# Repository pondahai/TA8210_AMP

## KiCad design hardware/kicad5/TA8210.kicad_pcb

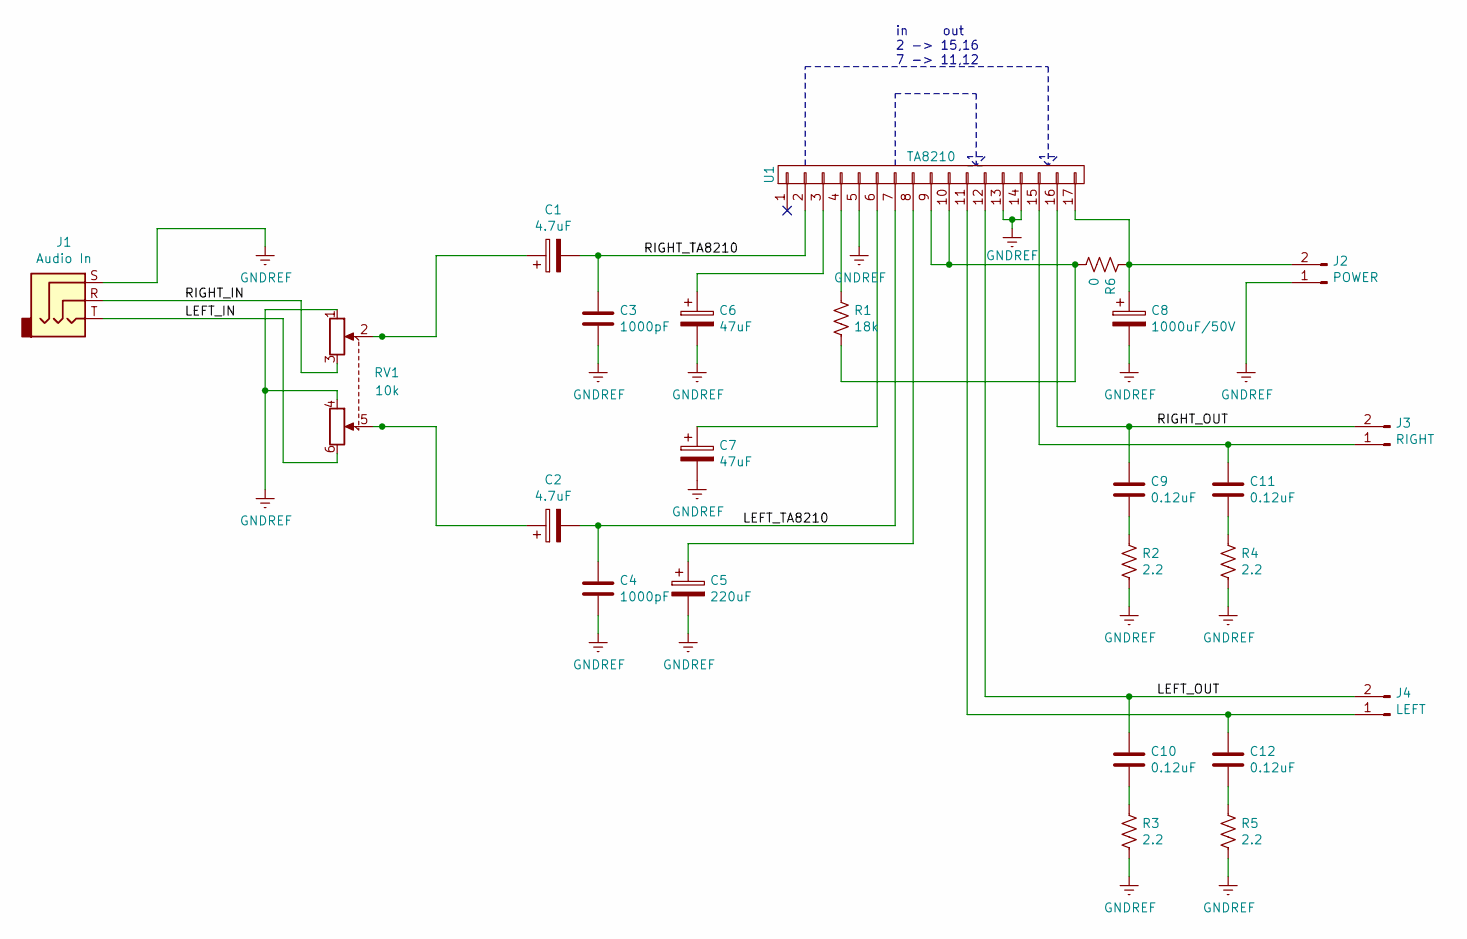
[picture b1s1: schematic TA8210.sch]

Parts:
C1, C2: 4.7uF; C_Rect_L13.0mm_W4.0mm_P10.00mm_FKS3_FKP3_MKS4
C3, C4: 1000pF; C_Disc_D10.5mm_W5.0mm_P5.00mm
C5: 220uF; CP_Radial_D10.0mm_P5.00mm
C6, C7: 47uF; CP_Radial_D10.0mm_P5.00mm
C8: 1000uF/50V; CP_Radial_D25.0mm_P10.00mm_SnapIn
C9, C10, C11, C12: 0.12uF; C_Disc_D9.0mm_W5.0mm_P5.00mm
J1: Audio In; audiojack-3.5mm-5p
J2: POWER; PhoenixContact_MSTBVA_2,5_2-G_1x02_P5.00mm_Vertical
J3: RIGHT; PhoenixContact_MSTBA_2,5_2-G_1x02_P5.00mm_Horizontal
J4: LEFT; PhoenixContact_MSTBA_2,5_2-G_1x02_P5.00mm_Horizontal
R1: 18k; R_Axial_DIN0207_L6.3mm_D2.5mm_P15.24mm_Horizontal
R2, R3, R4, R5: 2.2; R_Axial_DIN0207_L6.3mm_D2.5mm_P15.24mm_Horizontal
R6: 0; R_Axial_DIN0207_L6.3mm_D2.5mm_P15.24mm_Horizontal
RV1: 10k; Potentiometer_Alps_RK163_Dual_Horizontal
U1: TA8210; HZIP17-P-2.00

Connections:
/LEFT_IN: J1.T, RV1.6
/LEFT_OUT: C10.1, J4.2, U1.12
/LEFT_TA8210: C2.2, C4.1, U1.7
/RIGHT_IN: J1.R, RV1.3
/RIGHT_OUT: C9.1, J3.2, U1.16
/RIGHT_TA8210: C1.2, C3.1, U1.2
GNDREF: C3.2, C4.2, C5.2, C6.2, C7.2, C8.2, J1.S, J2.1, R2.2, R3.2, R4.2, R5.2, RV1.1, RV1.4, U1.5, U1.13, U1.14
unnamed: C1.1, RV1.2
unnamed: C2.1, RV1.5
unnamed: C5.1, U1.8
unnamed: C6.1, U1.3
unnamed: C7.1, U1.6
unnamed: C8.1, J2.2, R6.2, U1.17
unnamed: C9.2, R2.1
unnamed: C10.2, R3.1
unnamed: C11.1, J3.1, U1.15
unnamed: C11.2, R4.1
unnamed: C12.1, J4.1, U1.11
unnamed: C12.2, R5.1
unnamed: R1.1, R6.1, U1.9, U1.10
unnamed: R1.2, U1.4

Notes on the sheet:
in out 2 -> 15,16 7 -> 11,12

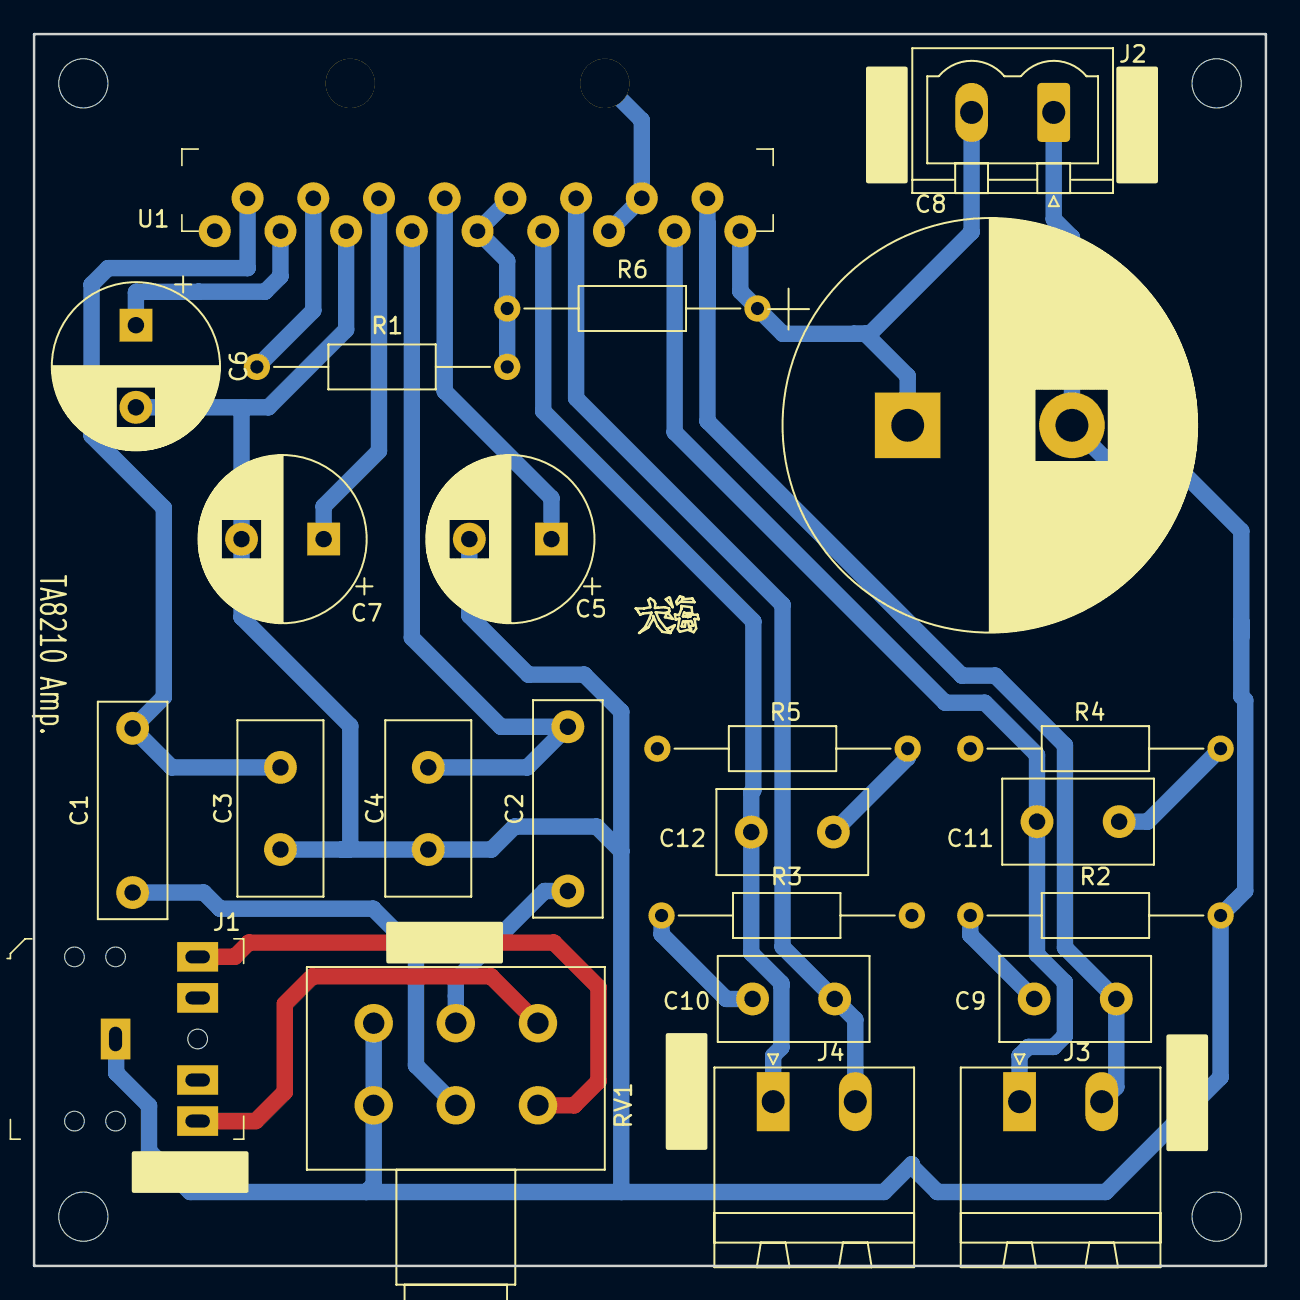
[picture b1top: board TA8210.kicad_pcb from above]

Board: 2 copper layers, 75.0 x 75.0 mm, 24 parts (0 on the bottom side), 21 nets.
